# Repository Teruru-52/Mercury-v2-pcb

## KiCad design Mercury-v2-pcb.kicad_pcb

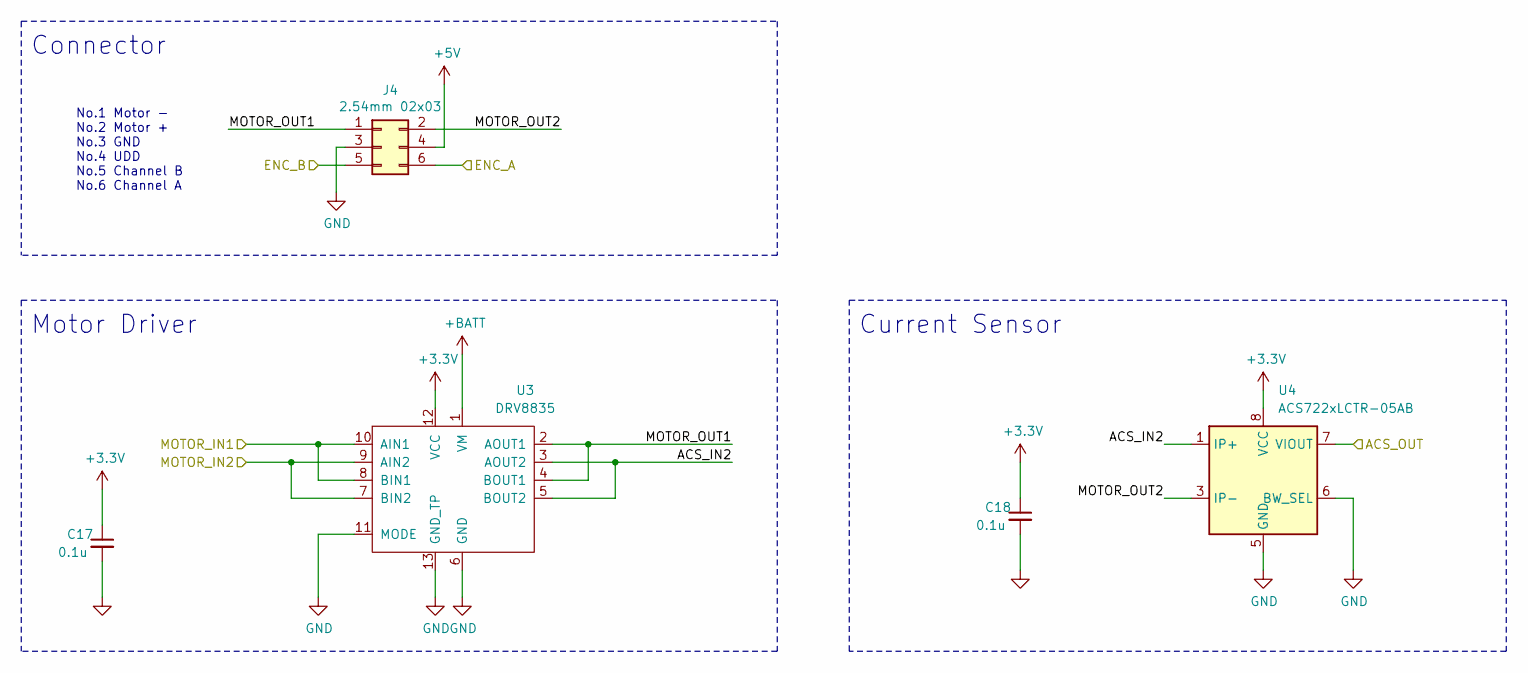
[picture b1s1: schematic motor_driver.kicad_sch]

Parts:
C17, C18: 0.1u; C_0201_0603Metric
J4: 2.54mm 02x03; PinHeader_2x03_P2.54mm_Vertical
U3: DRV8835; DRV8835DSSR
U4: ACS722xLCTR-05AB; SOIC-8_3.9x4.9mm_P1.27mm

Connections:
+3.3V: C17.1, C18.1, U3.12 (VCC), U4.8 (VCC); also elsewhere on the board
+5V: J4.4; also elsewhere on the board
+BATT: U3.1 (VM); also elsewhere on the board
/mcu/ACS_IN_L: U4.7 (VIOUT); also elsewhere on the board
/mcu/ENC_L_A: J4.6; also elsewhere on the board
/mcu/END_L_B: J4.5; also elsewhere on the board
/mcu/MOTOR_L_IN1: U3.8 (BIN1), U3.10 (AIN1); also elsewhere on the board
/mcu/MOTOR_L_IN2: U3.7 (BIN2), U3.9 (AIN2); also elsewhere on the board
/motor_driver L/ACS_IN2: U3.3 (AOUT2), U3.5 (BOUT2), U4.1 (IP+), U4.2 (IP+)
/motor_driver L/MOTOR_OUT1: J4.1, U3.2 (AOUT1), U3.4 (BOUT1)
/motor_driver L/MOTOR_OUT2: J4.2, U4.3 (IP-), U4.4 (IP-)
GND: C17.2, C18.2, J4.3, U3.6 (GND), U3.11 (MODE), U3.13 (GND_TP), U4.5 (GND), U4.6 (BW_SEL); also elsewhere on the board

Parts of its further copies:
C39, C40: 0.1u; C_0201_0603Metric
J7: 2.54mm 02x03; PinHeader_2x03_P2.54mm_Vertical
U11: DRV8835; DRV8835DSSR
U12: ACS722xLCTR-05AB; SOIC-8_3.9x4.9mm_P1.27mm

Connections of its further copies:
+3.3V: C39.1, C40.1, U11.12 (VCC), U12.8 (VCC); also elsewhere on the board
+5V: J7.4; also elsewhere on the board
+BATT: U11.1 (VM); also elsewhere on the board
/mcu/ACS_IN_R: U12.7 (VIOUT); also elsewhere on the board
/mcu/ENC_R_A: J7.6; also elsewhere on the board
/mcu/END_R_B: J7.5; also elsewhere on the board
/mcu/MOTOR_R_IN1: U11.8 (BIN1), U11.10 (AIN1); also elsewhere on the board
/mcu/MOTOR_R_IN2: U11.7 (BIN2), U11.9 (AIN2); also elsewhere on the board
/motor_driver R/ACS_IN2: U11.3 (AOUT2), U11.5 (BOUT2), U12.1 (IP+), U12.2 (IP+)
/motor_driver R/MOTOR_OUT1: J7.1, U11.2 (AOUT1), U11.4 (BOUT1)
/motor_driver R/MOTOR_OUT2: J7.2, U12.3 (IP-), U12.4 (IP-)
GND: C39.2, C40.2, J7.3, U11.6 (GND), U11.11 (MODE), U11.13 (GND_TP), U12.5 (GND), U12.6 (BW_SEL); also elsewhere on the board

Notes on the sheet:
Connector
No.1 Motor - No.2 Motor + No.3 GND No.4 UDD No.5 Channel B No.6 Channel A
Current Sensor
Motor Driver

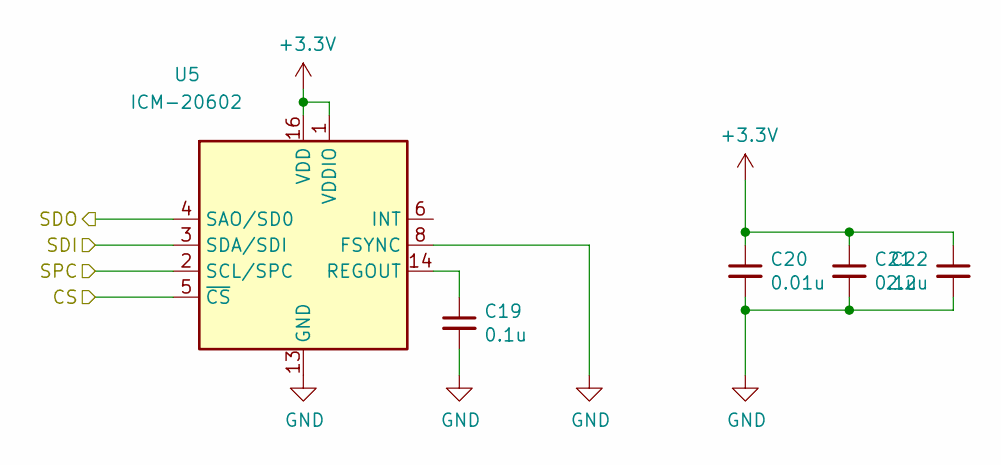
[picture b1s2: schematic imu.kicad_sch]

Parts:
C19, C21: 0.1u; C_0201_0603Metric
C20: 0.01u; C_0201_0603Metric
C22: 2.2u; C_0402_1005Metric
U5: ICM-20602; LGA-16_3x3mm_P0.5mm_LayoutBorder3x5y

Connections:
+3.3V: C20.1, C21.1, C22.1, U5.1 (VDDIO), U5.16 (VDD); also elsewhere on the board
/imu/CS: U5.5 (~CS); also elsewhere on the board
/imu/SDI: U5.3 (SDA/SDI); also elsewhere on the board
/imu/SDO: U5.4 (SAO/SD0); also elsewhere on the board
/imu/SPC: U5.2 (SCL/SPC); also elsewhere on the board
GND: C19.2, C20.2, C21.2, C22.2, U5.8 (FSYNC), U5.9 (GND), U5.10 (GND), U5.11 (GND), U5.12 (GND), U5.13 (GND), U5.15 (GND); also elsewhere on the board
unnamed: C19.1, U5.14 (REGOUT)

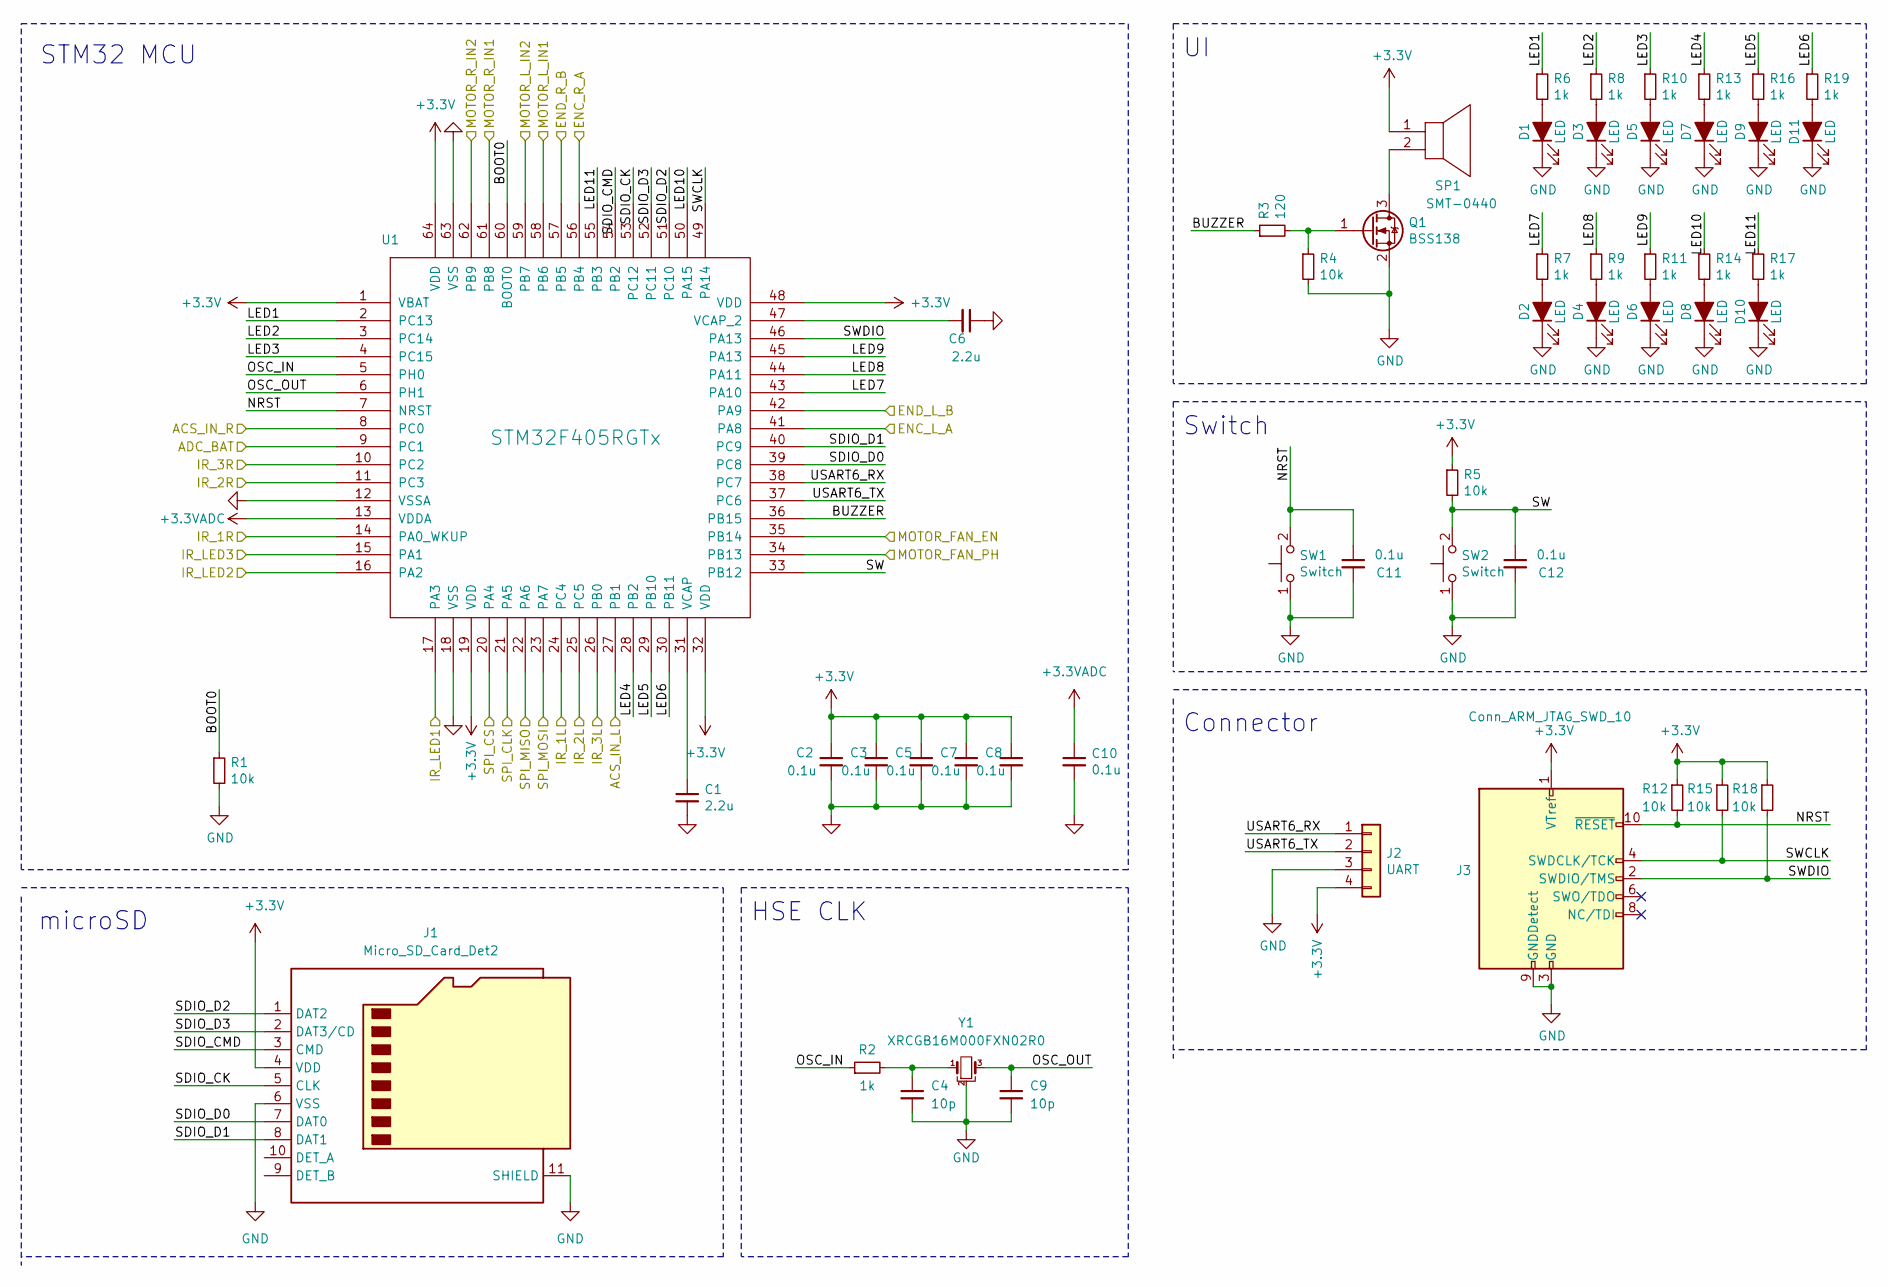
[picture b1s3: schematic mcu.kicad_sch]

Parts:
C1, C6: 2.2u; C_0402_1005Metric
C2, C3, C5, C7, C8, C10, C11, C12: 0.1u; C_0201_0603Metric
C4, C9: 10p; C_0402_1005Metric_Pad0.74x0.62mm_HandSolder
D1, D2, D3, D4, D5, D6, D7, D8, D9, D10, D11: LED; LED_0402_1005Metric
J1: Micro_SD_Card_Det2; microSD_HC_Hirose_DM3BT-DSF-PEJS
J2: UART; PinHeader_1x04_P2.54mm_Vertical
J3: Conn_ARM_JTAG_SWD_10; mylib
Q1: BSS138; SOT-23
R1, R4, R5, R12, R15, R18: 10k; R_0201_0603Metric
R2: 1k; R_0402_1005Metric_Pad0.72x0.64mm_HandSolder
R3: 120; R_0201_0603Metric
R6, R7, R8, R9, R10, R11, R13, R14, R16, R17, R19: 1k; R_0201_0603Metric
SP1: SMT-0440
SW1, SW2: Switch; TVAF06A020BR
U1: STM32F405RGTx; LQFP-64_10x10mm_P0.5mm
Y1: XRCGB16M000FXN02R0

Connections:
+3.3V: C2.1, C3.1, C5.1, C7.1, C8.1, J1.4 (VDD), J2.4, J3.1 (VTref), R5.1, R12.1, R15.1, R18.1, SP1.1, U1.1 (VBAT), U1.19 (VDD), U1.32 (VDD), U1.48 (VDD), U1.64 (VDD); also elsewhere on the board
+3.3VADC: C10.1, U1.13 (VDDA); also elsewhere on the board
/fan_driver/MOTOR_FAN_EN: U1.35 (PB14); also elsewhere on the board
/fan_driver/MOTOR_FAN_PH: U1.34 (PB13); also elsewhere on the board
/imu/CS: U1.20 (PA4); also elsewhere on the board
/imu/SDI: U1.23 (PA7); also elsewhere on the board
/imu/SDO: U1.22 (PA6); also elsewhere on the board
/imu/SPC: U1.21 (PA5); also elsewhere on the board
/ir_led/IR_LED_IN1: U1.16 (PA2); also elsewhere on the board
/ir_led/IR_LED_IN2: U1.15 (PA1); also elsewhere on the board
/ir_led_single/IR_LED_IN: U1.17 (PA3); also elsewhere on the board
/ir_sensor1/IR_OUT_A: U1.11 (PC3); also elsewhere on the board
/ir_sensor1/IR_OUT_B: U1.25 (PC5); also elsewhere on the board
/ir_sensor2/IR_OUT_A: U1.10 (PC2); also elsewhere on the board
/ir_sensor2/IR_OUT_B: U1.26 (PB0); also elsewhere on the board
/ir_sensor/IR_OUT_A: U1.14 (PA0_WKUP); also elsewhere on the board
/ir_sensor/IR_OUT_B: U1.24 (PC4); also elsewhere on the board
/mcu/ACS_IN_L: U1.27 (PB1); also elsewhere on the board
/mcu/ACS_IN_R: U1.8 (PC0); also elsewhere on the board
/mcu/ADC_BAT: U1.9 (PC1); also elsewhere on the board
/mcu/BOOT0: R1.1, U1.60 (BOOT0)
/mcu/BUZZER: R3.1, U1.36 (PB15)
/mcu/ENC_L_A: U1.41 (PA8); also elsewhere on the board
/mcu/ENC_R_A: U1.56 (PB4); also elsewhere on the board
/mcu/END_L_B: U1.42 (PA9); also elsewhere on the board
/mcu/END_R_B: U1.57 (PB5); also elsewhere on the board
/mcu/LED1: R6.1, U1.2 (PC13)
/mcu/LED2: R8.1, U1.3 (PC14)
/mcu/LED3: R10.1, U1.4 (PC15)
/mcu/LED4: R13.1, U1.28 (PB2)
/mcu/LED5: R16.1, U1.29 (PB10)
/mcu/LED6: R19.1, U1.30 (PB11)
/mcu/LED7: R7.1, U1.43 (PA10)
/mcu/LED8: R9.1, U1.44 (PA11)
/mcu/LED9: R11.1, U1.45 (PA13)
/mcu/LED10: R14.1, U1.50 (PA15)
/mcu/LED11: R17.1, U1.55 (PB3)
/mcu/MOTOR_L_IN1: U1.58 (PB6); also elsewhere on the board
/mcu/MOTOR_L_IN2: U1.59 (PB7); also elsewhere on the board
/mcu/MOTOR_R_IN1: U1.61 (PB8); also elsewhere on the board
/mcu/MOTOR_R_IN2: U1.62 (PB9); also elsewhere on the board
/mcu/NRST: C11.1, J3.10 (~RESET), R12.2, SW1.2, U1.7 (NRST)
/mcu/OSC_IN: R2.1, U1.5 (PH0)
/mcu/OSC_OUT: C9.1, U1.6 (PH1), Y1.3
/mcu/SDIO_CK: J1.5 (CLK), U1.53 (PC12)
/mcu/SDIO_CMD: J1.3 (CMD), U1.54 (PB2)
/mcu/SDIO_D0: J1.7 (DAT0), U1.39 (PC8)
/mcu/SDIO_D1: J1.8 (DAT1), U1.40 (PC9)
/mcu/SDIO_D2: J1.1 (DAT2), U1.51 (PC10)
/mcu/SDIO_D3: J1.2 (DAT3/CD), U1.52 (PC11)
/mcu/SW: C12.1, R5.2, SW2.2, U1.33 (PB12)
/mcu/SWCLK: J3.4 (SWDCLK/TCK), R15.2, U1.49 (PA14)
/mcu/SWDIO: J3.2 (SWDIO/TMS), R18.2, U1.46 (PA13)
/mcu/USART6_RX: J2.1, U1.38 (PC7)
/mcu/USART6_TX: J2.2, U1.37 (PC6)
GND: C1.2, C2.2, C3.2, C4.2, C5.2, C6.1, C7.2, C8.2, C9.2, C10.2, C11.2, C12.2, D1.1 (K), D2.1 (K), D3.1 (K), D4.1 (K), D5.1 (K), D6.1 (K), D7.1 (K), D8.1 (K), D9.1 (K), D10.1 (K), D11.1 (K), J1.6 (VSS), J1.11 (SHIELD), J2.3, J3.3 (GND), J3.5 (GND), J3.9 (GNDDetect), Q1.2 (S), R1.2, R4.2, SW1.1, SW2.1, U1.12 (VSSA), U1.18 (VSS), U1.63 (VSS), Y1.2; also elsewhere on the board
unnamed: C4.1, R2.2, Y1.1
unnamed: D1.2 (A), R6.2
unnamed: D2.2 (A), R7.2
unnamed: D3.2 (A), R8.2
unnamed: D4.2 (A), R9.2
unnamed: D5.2 (A), R10.2
unnamed: D6.2 (A), R11.2
unnamed: D7.2 (A), R13.2
unnamed: D8.2 (A), R14.2
unnamed: D9.2 (A), R16.2
unnamed: D10.2 (A), R17.2
unnamed: D11.2 (A), R19.2
unnamed: Q1.3 (D), SP1.2
unnamed: Q1.1 (G), R3.2, R4.1
unnamed: C1.1, U1.31 (VCAP)
unnamed: C6.2, U1.47 (VCAP_2)

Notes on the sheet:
STM32 MCU
microSD
Connector
HSE CLK
Switch

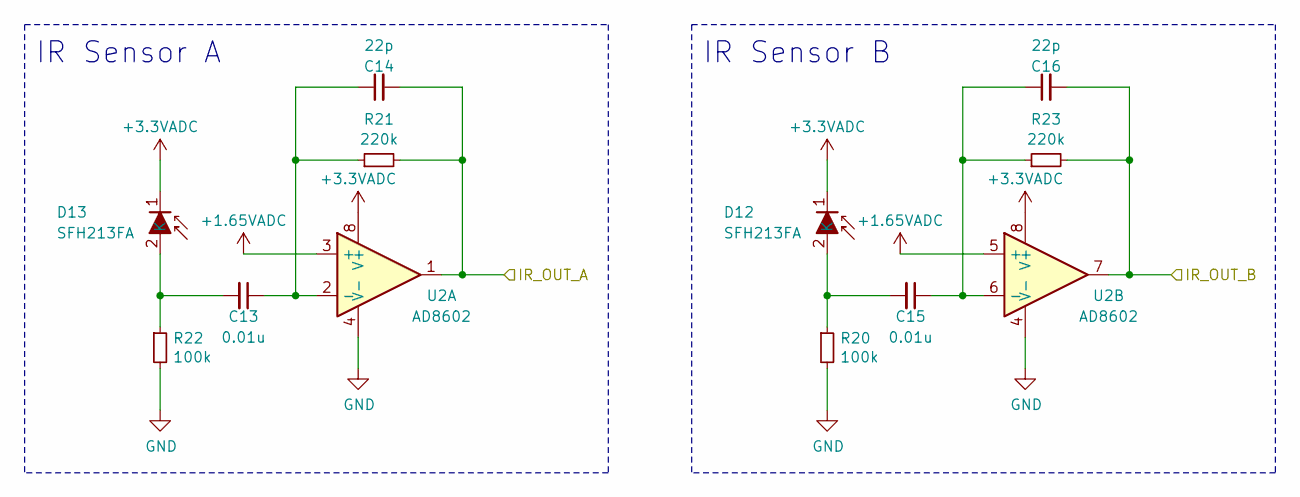
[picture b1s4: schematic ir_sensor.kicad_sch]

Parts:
C13, C15: 0.01u; C_0201_0603Metric
C14, C16: 22p; C_0201_0603Metric
D12, D13: SFH213FA; D_T-1_P2.54mm_Vertical_AnodeUp
R20, R22: 100k; R_0603_1608Metric
R21, R23: 220k; R_0201_0603Metric
U2: AD8602; MSOP-8_3x3mm_P0.65mm

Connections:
+1.65VADC: U2.3 (+), U2.5 (+); also elsewhere on the board
+3.3VADC: D12.1 (K), D13.1 (K), U2.8 (V+); also elsewhere on the board
/ir_sensor/IR_OUT_A: C14.2, R21.2, U2.1; also elsewhere on the board
/ir_sensor/IR_OUT_B: C16.2, R23.2, U2.7; also elsewhere on the board
GND: R20.2, R22.2, U2.4 (V-); also elsewhere on the board
unnamed: C13.2, D13.2, R22.1
unnamed: C15.2, D12.2, R20.1
unnamed: C13.1, C14.1, R21.1, U2.2 (-)
unnamed: C15.1, C16.1, R23.1, U2.6 (-)

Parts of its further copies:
C31, C33, C35, C37: 0.01u; C_0201_0603Metric
C32, C34, C36, C38: 22p; C_0201_0603Metric
D19, D20, D21, D22: SFH213FA; D_T-1_P2.54mm_Vertical_AnodeUp
R38, R40, R42, R44: 100k; R_0603_1608Metric
R39, R41, R43, R45: 220k; R_0201_0603Metric
U9, U10: AD8602; MSOP-8_3x3mm_P0.65mm

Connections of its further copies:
+1.65VADC: U9.3 (+), U9.5 (+), U10.3 (+), U10.5 (+); also elsewhere on the board
+3.3VADC: D19.1 (K), D20.1 (K), D21.1 (K), D22.1 (K), U9.8 (V+), U10.8 (V+); also elsewhere on the board
/ir_sensor1/IR_OUT_A: C32.2, R39.2, U9.1; also elsewhere on the board
/ir_sensor1/IR_OUT_B: C34.2, R41.2, U9.7; also elsewhere on the board
/ir_sensor2/IR_OUT_A: C36.2, R43.2, U10.1; also elsewhere on the board
/ir_sensor2/IR_OUT_B: C38.2, R45.2, U10.7; also elsewhere on the board
GND: R38.2, R40.2, R42.2, R44.2, U9.4 (V-), U10.4 (V-); also elsewhere on the board
unnamed: C31.2, D20.2, R40.1
unnamed: C33.2, D19.2, R38.1
unnamed: C35.2, D22.2, R44.1
unnamed: C37.2, D21.2, R42.1
unnamed: C31.1, C32.1, R39.1, U9.2 (-)
unnamed: C33.1, C34.1, R41.1, U9.6 (-)
unnamed: C35.1, C36.1, R43.1, U10.2 (-)
unnamed: C37.1, C38.1, R45.1, U10.6 (-)

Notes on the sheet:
IR Sensor B
IR Sensor A

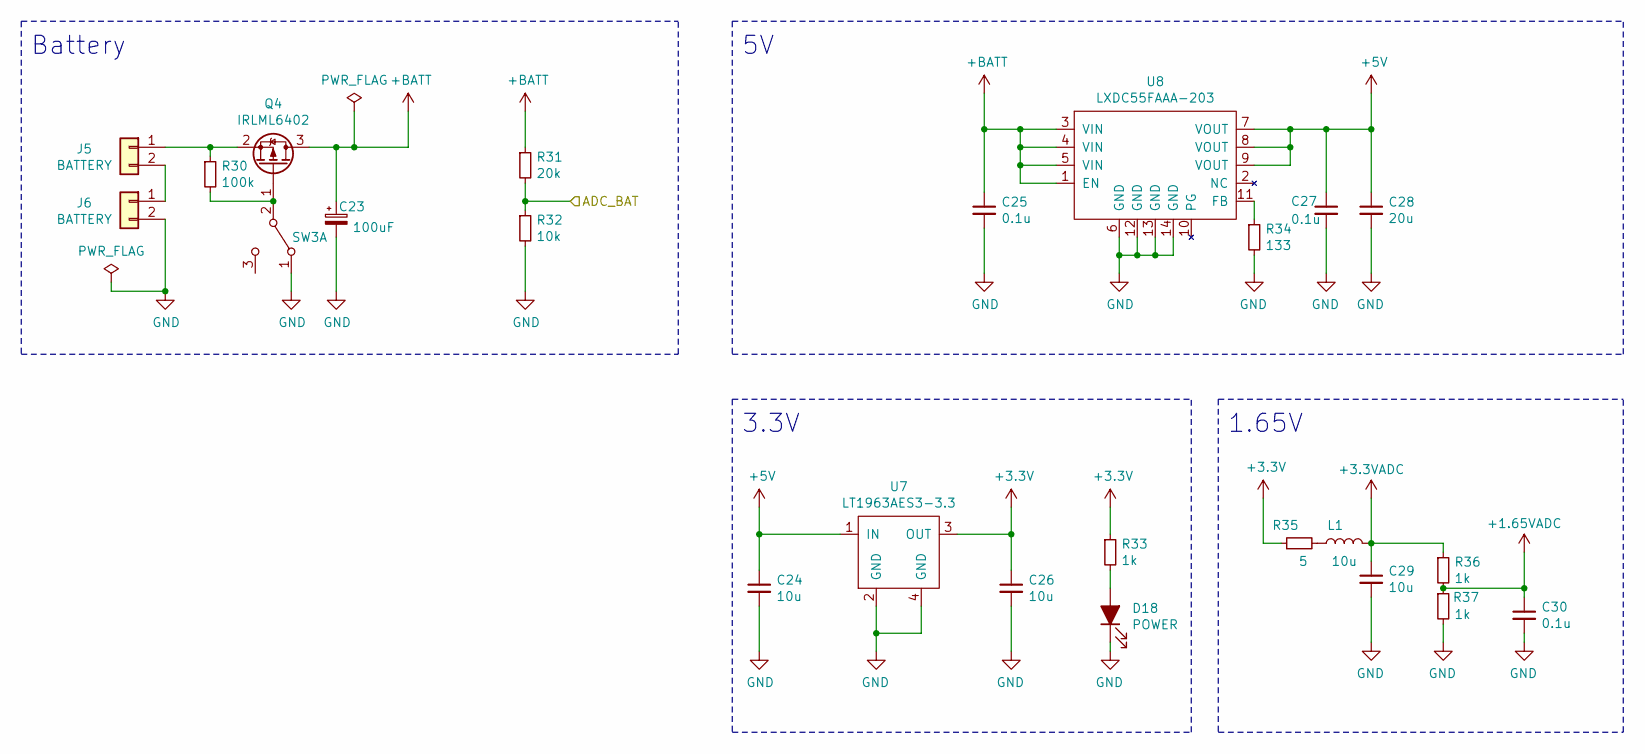
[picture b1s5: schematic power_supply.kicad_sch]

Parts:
C23: 100uF; CP_Elec_6.3x3
C24, C26: 10u; C_0805_2012Metric
C25, C27: 0.1u; C_0603_1608Metric_Pad1.08x0.95mm_HandSolder
C28: 20u; C_0603_1608Metric_Pad1.08x0.95mm_HandSolder
C29: 10u; C_0603_1608Metric_Pad1.08x0.95mm_HandSolder
C30: 0.1u; C_0201_0603Metric
D18: POWER; LED_0402_1005Metric
J5, J6: BATTERY; PinSocket_1x02_P1.27mm_Vertical
L1: 10u; L_1008_2520Metric
Q4: IRLML6402; SOT-23
R30: 100k; R_0603_1608Metric
R31: 20k; R_0402_1005Metric
R32: 10k; R_0402_1005Metric
R33: 1k; R_0201_0603Metric
R34: 133; R_1206_3216Metric_Pad1.30x1.75mm_HandSolder
R35: 5; R_0805_2012Metric_Pad1.20x1.40mm_HandSolder
R36, R37: 1k; R_0603_1608Metric
SW3: SW_DPDT_x2; PinHeader_1x03_P2.54mm_Vertical
U7: LT1963AES3-3.3; SOT-223
U8: LXDC55FAAA-203; LXDC55FAAA203

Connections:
+1.65VADC: C30.1, R36.2, R37.1; also elsewhere on the board
+3.3V: C26.1, R33.1, R35.1, U7.3 (OUT); also elsewhere on the board
+3.3VADC: C29.1, L1.2, R36.1; also elsewhere on the board
+5V: C24.1, C27.1, C28.1, U7.1 (IN), U8.7 (VOUT), U8.8 (VOUT), U8.9 (VOUT); also elsewhere on the board
+BATT: C23.1, C25.1, Q4.3 (D), R31.1, U8.1 (EN), U8.3 (VIN), U8.4 (VIN), U8.5 (VIN); also elsewhere on the board
/mcu/ADC_BAT: R31.2, R32.1; also elsewhere on the board
GND: C23.2, C24.2, C25.2, C26.2, C27.2, C28.2, C29.2, C30.2, D18.1 (K), J6.2, R32.2, R34.2, R37.2, SW3.1 (A), U7.2 (GND), U7.4 (GND), U8.6 (GND), U8.12 (GND), U8.13 (GND), U8.14 (GND); also elsewhere on the board
unnamed: D18.2 (A), R33.2
unnamed: J5.1, Q4.2 (S), R30.1
unnamed: J5.2, J6.1
unnamed: L1.1, R35.2
unnamed: Q4.1 (G), R30.2, SW3.2 (B)
unnamed: R34.1, U8.11 (FB)

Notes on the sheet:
3.3V
1.65V
Battery

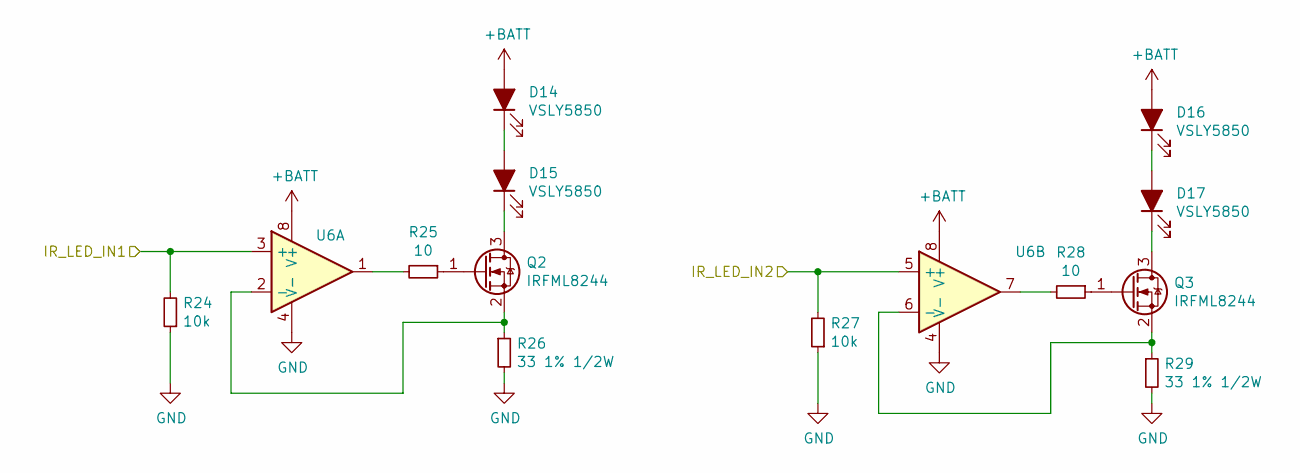
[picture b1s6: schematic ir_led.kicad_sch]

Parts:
D14, D15, D16, D17: VSLY5850; D_T-1_P2.54mm_Vertical_AnodeUp
Q2, Q3: IRFML8244; SOT-23
R24, R27: 10k; R_0201_0603Metric
R25, R28: 10; R_0603_1608Metric
R26, R29: 33 1% 1/2W; R_0603_1608Metric
U6: SOIC-8_3.9x4.9mm_P1.27mm

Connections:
+BATT: D14.2 (A), D16.2 (A), U6.8 (V+); also elsewhere on the board
/ir_led/IR_LED_IN1: R24.2, U6.3 (+); also elsewhere on the board
/ir_led/IR_LED_IN2: R27.2, U6.5 (+); also elsewhere on the board
GND: R24.1, R26.2, R27.1, R29.2, U6.4 (V-); also elsewhere on the board
unnamed: D14.1 (K), D15.2 (A)
unnamed: D15.1 (K), Q2.3 (D)
unnamed: D16.1 (K), D17.2 (A)
unnamed: D17.1 (K), Q3.3 (D)
unnamed: Q2.1 (G), R25.1
unnamed: Q2.2 (S), R26.1, U6.2 (-)
unnamed: Q3.1 (G), R28.1
unnamed: Q3.2 (S), R29.1, U6.6 (-)
unnamed: R25.2, U6.1
unnamed: R28.2, U6.7

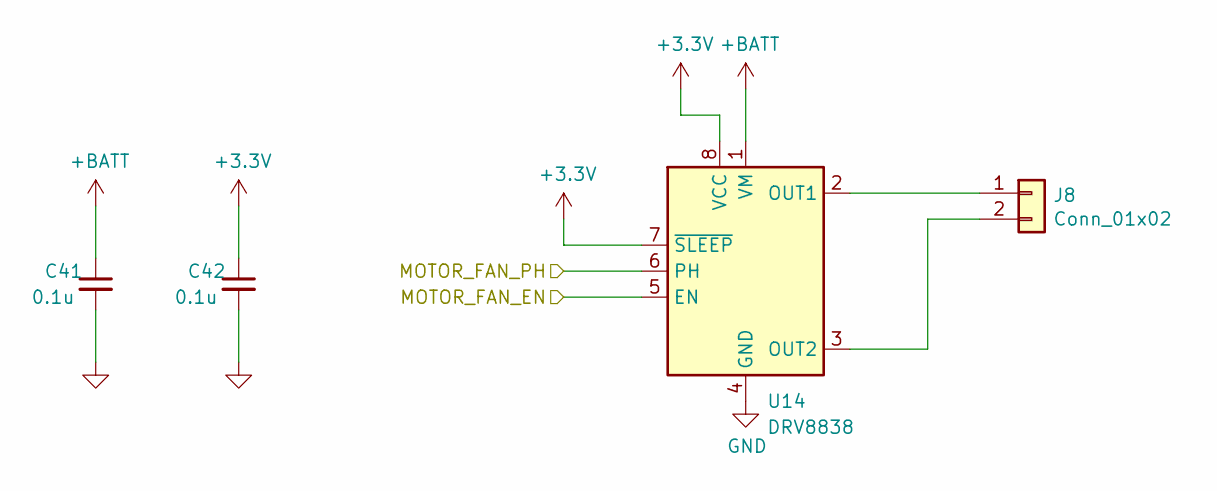
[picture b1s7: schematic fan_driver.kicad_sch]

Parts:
C41: 0.1u; C_0603_1608Metric
C42: 0.1u; C_0201_0603Metric
J8: Conn_01x02; PinSocket_1x02_P1.27mm_Vertical
U14: DRV8838; WSON-8-1EP_2x2mm_P0.5mm_EP0.9x1.6mm

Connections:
+3.3V: C42.1, U14.7 (~SLEEP), U14.8 (VCC); also elsewhere on the board
+BATT: C41.1, U14.1 (VM); also elsewhere on the board
/fan_driver/MOTOR_FAN_EN: U14.5 (EN); also elsewhere on the board
/fan_driver/MOTOR_FAN_PH: U14.6 (PH); also elsewhere on the board
GND: C41.2, C42.2, U14.4 (GND), U14.9 (GND); also elsewhere on the board
unnamed: J8.1, U14.2 (OUT1)
unnamed: J8.2, U14.3 (OUT2)

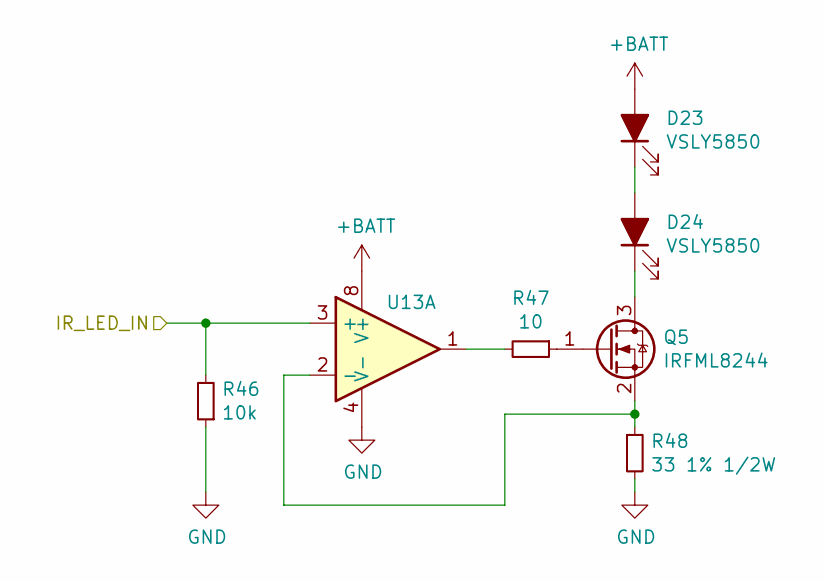
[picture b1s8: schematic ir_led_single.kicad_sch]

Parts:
D23, D24: VSLY5850; D_T-1_P2.54mm_Vertical_AnodeUp
Q5: IRFML8244; SOT-23
R46: 10k; R_0201_0603Metric
R47: 10; R_0603_1608Metric
R48: 33 1% 1/2W; R_0603_1608Metric
U13: SOIC-8_3.9x4.9mm_P1.27mm

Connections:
+BATT: D23.2 (A), U13.8 (V+); also elsewhere on the board
/ir_led_single/IR_LED_IN: R46.2, U13.3 (+); also elsewhere on the board
GND: R46.1, R48.2, U13.4 (V-); also elsewhere on the board
unnamed: D23.1 (K), D24.2 (A)
unnamed: D24.1 (K), Q5.3 (D)
unnamed: Q5.1 (G), R47.1
unnamed: Q5.2 (S), R48.1, U13.2 (-)
unnamed: R47.2, U13.1

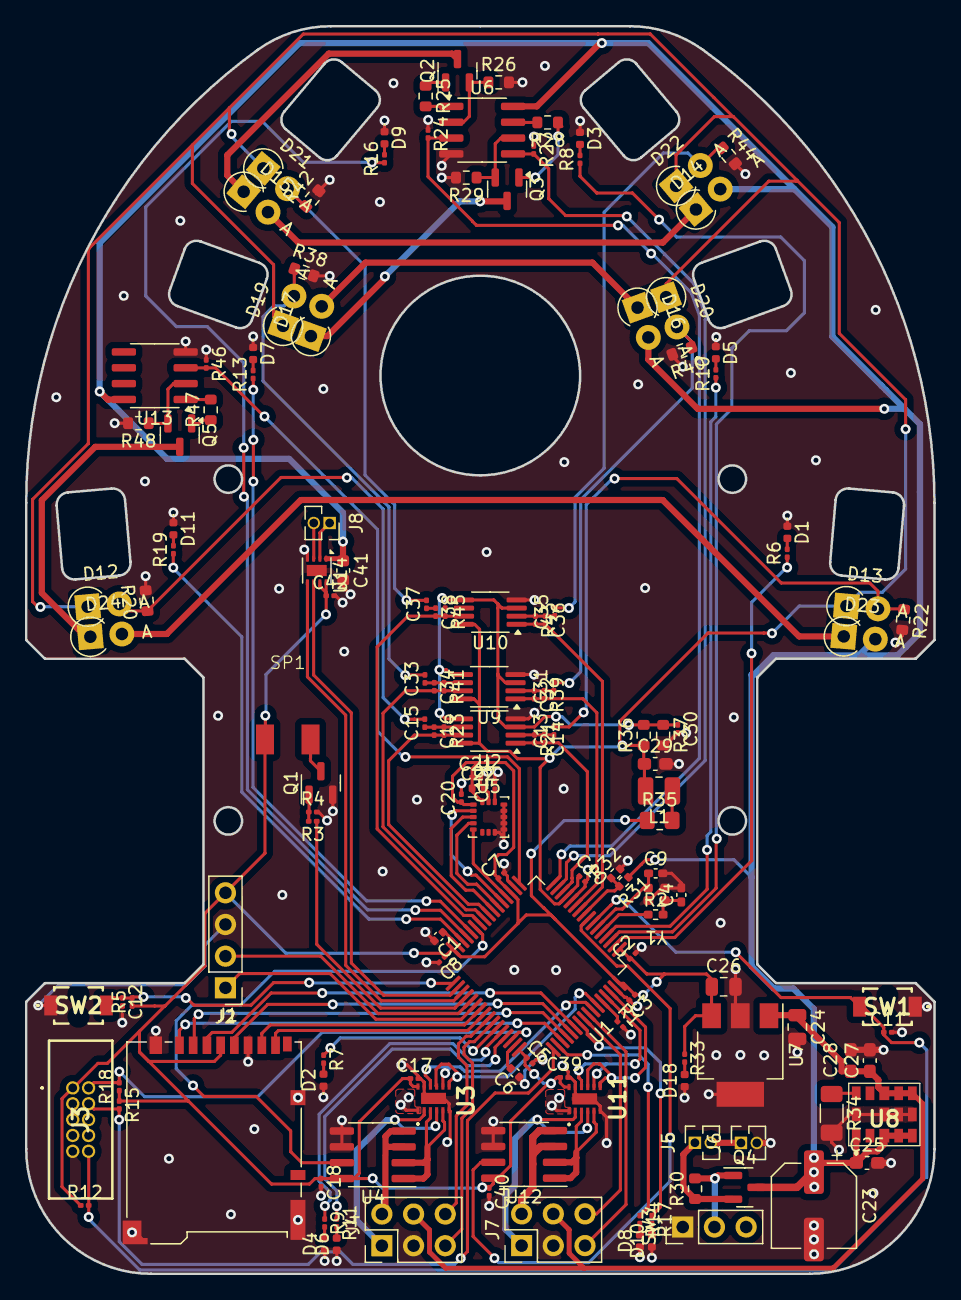
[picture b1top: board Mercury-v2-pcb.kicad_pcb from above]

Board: 2 copper layers, 72.8 x 100.0 mm, 147 parts (0 on the bottom side), 117 nets.

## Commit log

2024-08-07 feat: improve pcb
2024-08-08 feat: route tracks
2024-08-08 feat: add filled zone
2024-08-08 feat: finish zone and via
